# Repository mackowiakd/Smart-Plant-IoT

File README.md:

> 🎓 **Academic Project**: This project was developed for the *Microprocessor and Embedded Systems* course during the 5th semester of Computer Science at the **Silesian University of Technology** (Politechnika Śląska).

# Smart Plant Care IoT System 🌱

An end-to-end Internet of Things (IoT) solution for monitoring environmental parameters and autonomously managing plant hydration. The project spans custom hardware design (PCB), edge device firmware (ESP32-C3), and a full-stack web dashboard.

## 🌟 Key Features
* **Smart Autonomous Watering:** Activates a water pump based on custom-calibrated soil moisture data (`AIR_VALUE` & `WATER_VALUE`). The logic includes safety checks, such as preventing watering during low temperatures to protect the plant roots.
* **Extreme Power Optimization:** Heavily utilizes the ESP32 **Deep Sleep** mode. The system wakes up periodically, performs measurements, communicates with the server, and goes back to sleep, allowing for long-term operation on a standard 5V powerbank.
* **Fail-Safe Offline Mode (Fallback AP):** If the configured WiFi network is lost, the device automatically spawns its own Access Point (e.g., "Roslina SOS"). It serves a lightweight local HTML page (`WebPage.h`) directly to a smartphone, allowing the user to view telemetry without internet access.
* **Hybrid Timekeeping:** Combines internet time synchronization (NTP) with a battery-backed hardware Real-Time Clock (DS3231) to maintain time context and scheduling during power losses or offline periods.
* **Full-Stack SPA Architecture:** Telemetry is pushed via HTTP to a custom .NET backend, which seamlessly serves a modern React-based user dashboard.

## 🛠️ System Architecture & Tech Stack

### 1. Edge Device (Firmware & Hardware)
* **Microcontroller:** Seeed Studio XIAO ESP32-C3.
* **Sensors & Actuators:** * **BME280** (Temperature, Humidity, Atmospheric Pressure) via I2C.
  * **BH1750** (Light intensity/Lux) via I2C.
  * **DS3231** (Hardware RTC) via I2C.
  * **Capacitive Soil Moisture Sensor v1.2** via ADC.
  * 5V Water Pump controlled via MOSFET/Relay.
* **Firmware:** C++, PlatformIO, custom sleep/wake routines.

### 2. Web Application (Backend & Frontend)
* **Architecture:** Single Page Application (SPA) integration.
* **Backend:** C#, ASP.NET Core REST API for telemetry data ingestion and aggregation.
* **Frontend:** React.js, Vite, and Tailwind CSS for responsive data visualization.

## 📸 Project Gallery

  **Figure 1: Custom PCB & Hardware Assembly.** *The physical implementation of the project. I designed the schematic and routed the custom PCB using **KiCad** to seamlessly integrate the XIAO ESP32-C3 with various modules: an I2C environment sensor array (including BH1750), a battery-backed RTC, and the power delivery circuitry. The entire system is optimized to run autonomously on a standard 5V powerbank utilizing Deep Sleep cycles.*

  **Figure 1: Custom PCB & Hardware Assembly.** Showing the XIAO ESP32-C3 integration with environmental sensors and the watering unit running on powerbank supply.

https://github.com/user-attachments/assets/34abda69-28c0-408e-982a-c36de282d4bd

  **Figure 2: React Dashboard.** Visualizing real-time telemetry data (humidity, temperature, pressure, light) received from the .NET REST API.

https://github.com/user-attachments/assets/e299edc5-c103-400d-92fd-4557b35e483f

  **Figure 3: Emergency Offline Mode.** The lightweight captive portal/HTML page served directly by the ESP32 when external WiFi is unavailable.

## 🚀

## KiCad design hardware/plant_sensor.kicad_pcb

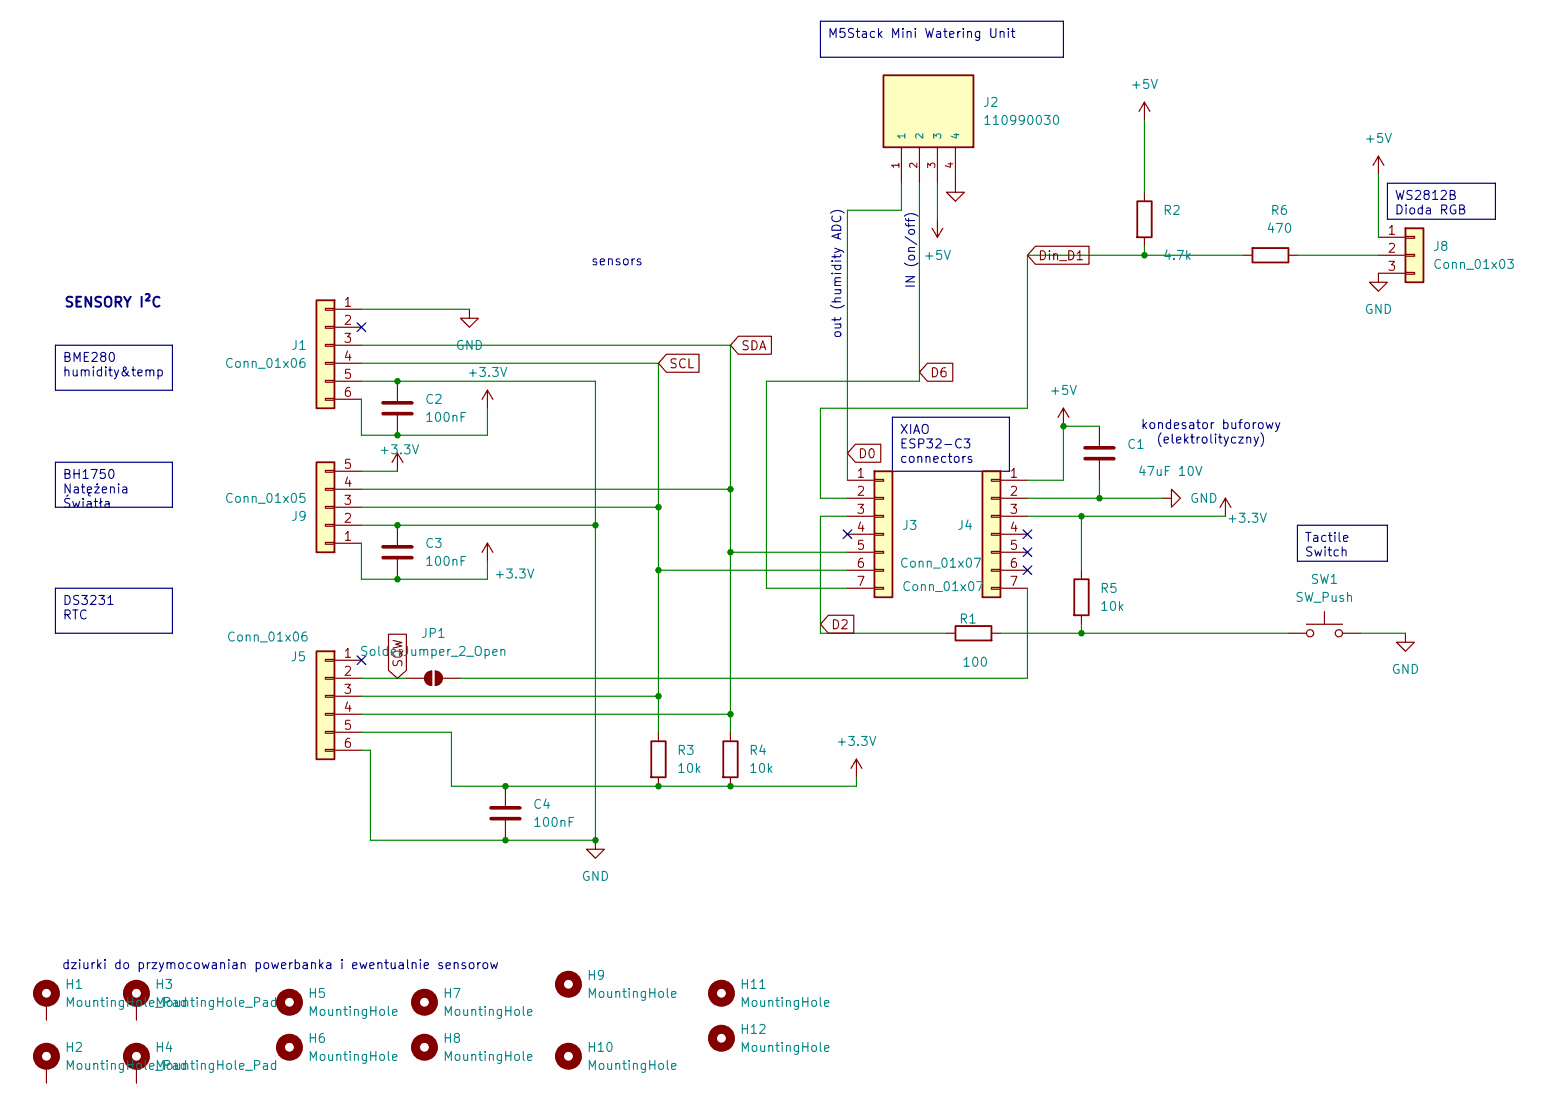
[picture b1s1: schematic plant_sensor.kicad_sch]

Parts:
C1: 47uF 10V; C_1206_3216Metric; LCSC Part # C13608
C2, C3, C4: 100nF; C_0805_2012Metric; LCSC Part # C49678
H1, H2, H3, H4: MountingHole_Pad; MountingHole_4.3mm_M4_Pad
H5, H6, H7, H8: MountingHole; MountingHole_2.7mm
H9, H10, H11, H12: MountingHole; MountingHole_2.5mm
J1, J5: Conn_01x06; PinHeader_1x06_P2.54mm_Vertical; LCSC Part # C50982
J2: 110990030; SEEED_110990030; PARTREV A; LCSC Part # C52230
J3, J4: Conn_01x07; PinHeader_1x07_P2.54mm_Vertical; LCSC Part # C2254
J8: Conn_01x03; PinHeader_1x03_P2.54mm_Vertical; LCSC Part # C124398
J9: Conn_01x05; PinHeader_1x05_P2.54mm_Vertical; LCSC Part # C2251
JP1: SolderJumper_2_Open; SolderJumper-2_P1.3mm_Open_RoundedPad1.0x1.5mm
R1: 100; R_0805_2012Metric; LCSC Part # C17408
R2: 4.7k; R_0805_2012Metric; LCSC Part # C17673
R3, R4, R5: 10k; R_0805_2012Metric; LCSC Part # C17414
R6: 470; R_0805_2012Metric; LCSC Part # C17710
SW1: SW_Push; SW_PUSH_6mm; LCSC Part # C318884

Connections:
+3.3V: C2.2, C3.2, C4.1, J1.6, J4.3, J5.5, J9.1, J9.5, R3.2, R4.2, R5.1
+5V: C1.1, J2.3, J4.1, J8.1, R2.1
D0: J2.1, J3.1
D2: J3.3, R1.1
D6: J2.2, J3.7
Din_D1: J3.2, R2.2, R6.2
GND: C1.2, C2.1, C3.1, C4.2, J1.1, J1.5, J2.4, J4.2, J5.6, J8.3, J9.2, SW1.2
unnamed: J4.7, JP1.2 (B)
unnamed: J8.2, R6.1
unnamed: R1.2, R5.2, SW1.1
SCL: J1.4, J3.6, J5.3, J9.3, R3.1
SDA: J1.3, J3.5, J5.4, J9.4, R4.1
SQW: J5.2, JP1.1 (A)

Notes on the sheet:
sensors
IN (on/off)
SENSORY I²C
dziurki do przymocowanian powerbanka i ewentualnie sensorow
kondesator buforowy (elektrolityczny)
out (humidity ADC)
M5Stack Mini Watering Unit
XIAO ESP32-C3 connectors
BME280 humidity&temp
WS2812B Dioda RGB
BH1750 Natężenia Światła
Tactile Switch
DS3231 RTC

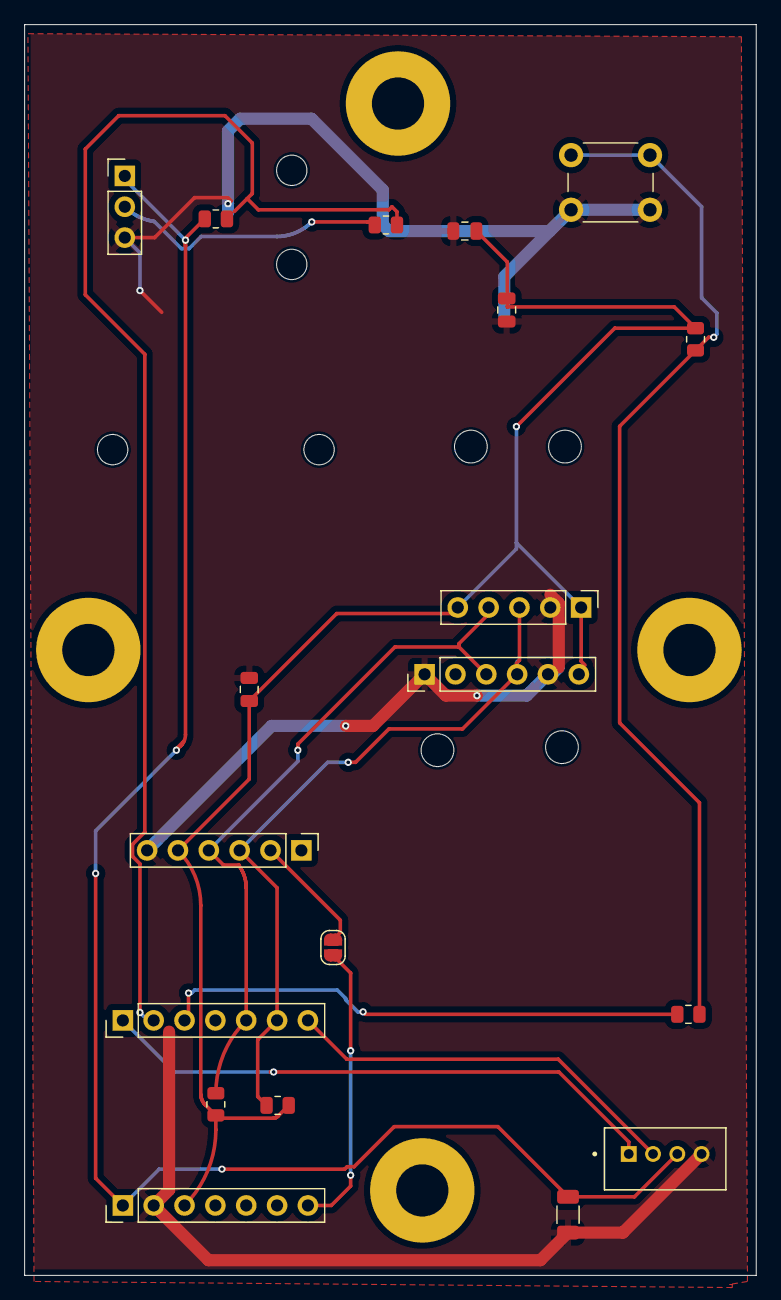
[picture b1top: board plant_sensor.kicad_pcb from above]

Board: 2 copper layers, 60.2 x 103.0 mm, 31 parts (0 on the bottom side), 13 nets.

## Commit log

2026-02-20 Initial commit: struktura End-to-End (Firmware, Web App, Hardware)
2026-02-20 Revise images and captions in project gallery
    Updated project gallery images and descriptions in README.
2026-02-24 Add custom PCB image and description to README
    Updated project gallery with a new image and description.
2026-03-05 Update README with image links for figures
    Added links to images for figures in the README.
2026-03-05 Replace outdated asset link in README
    Updated asset link in README.md to the latest version.
